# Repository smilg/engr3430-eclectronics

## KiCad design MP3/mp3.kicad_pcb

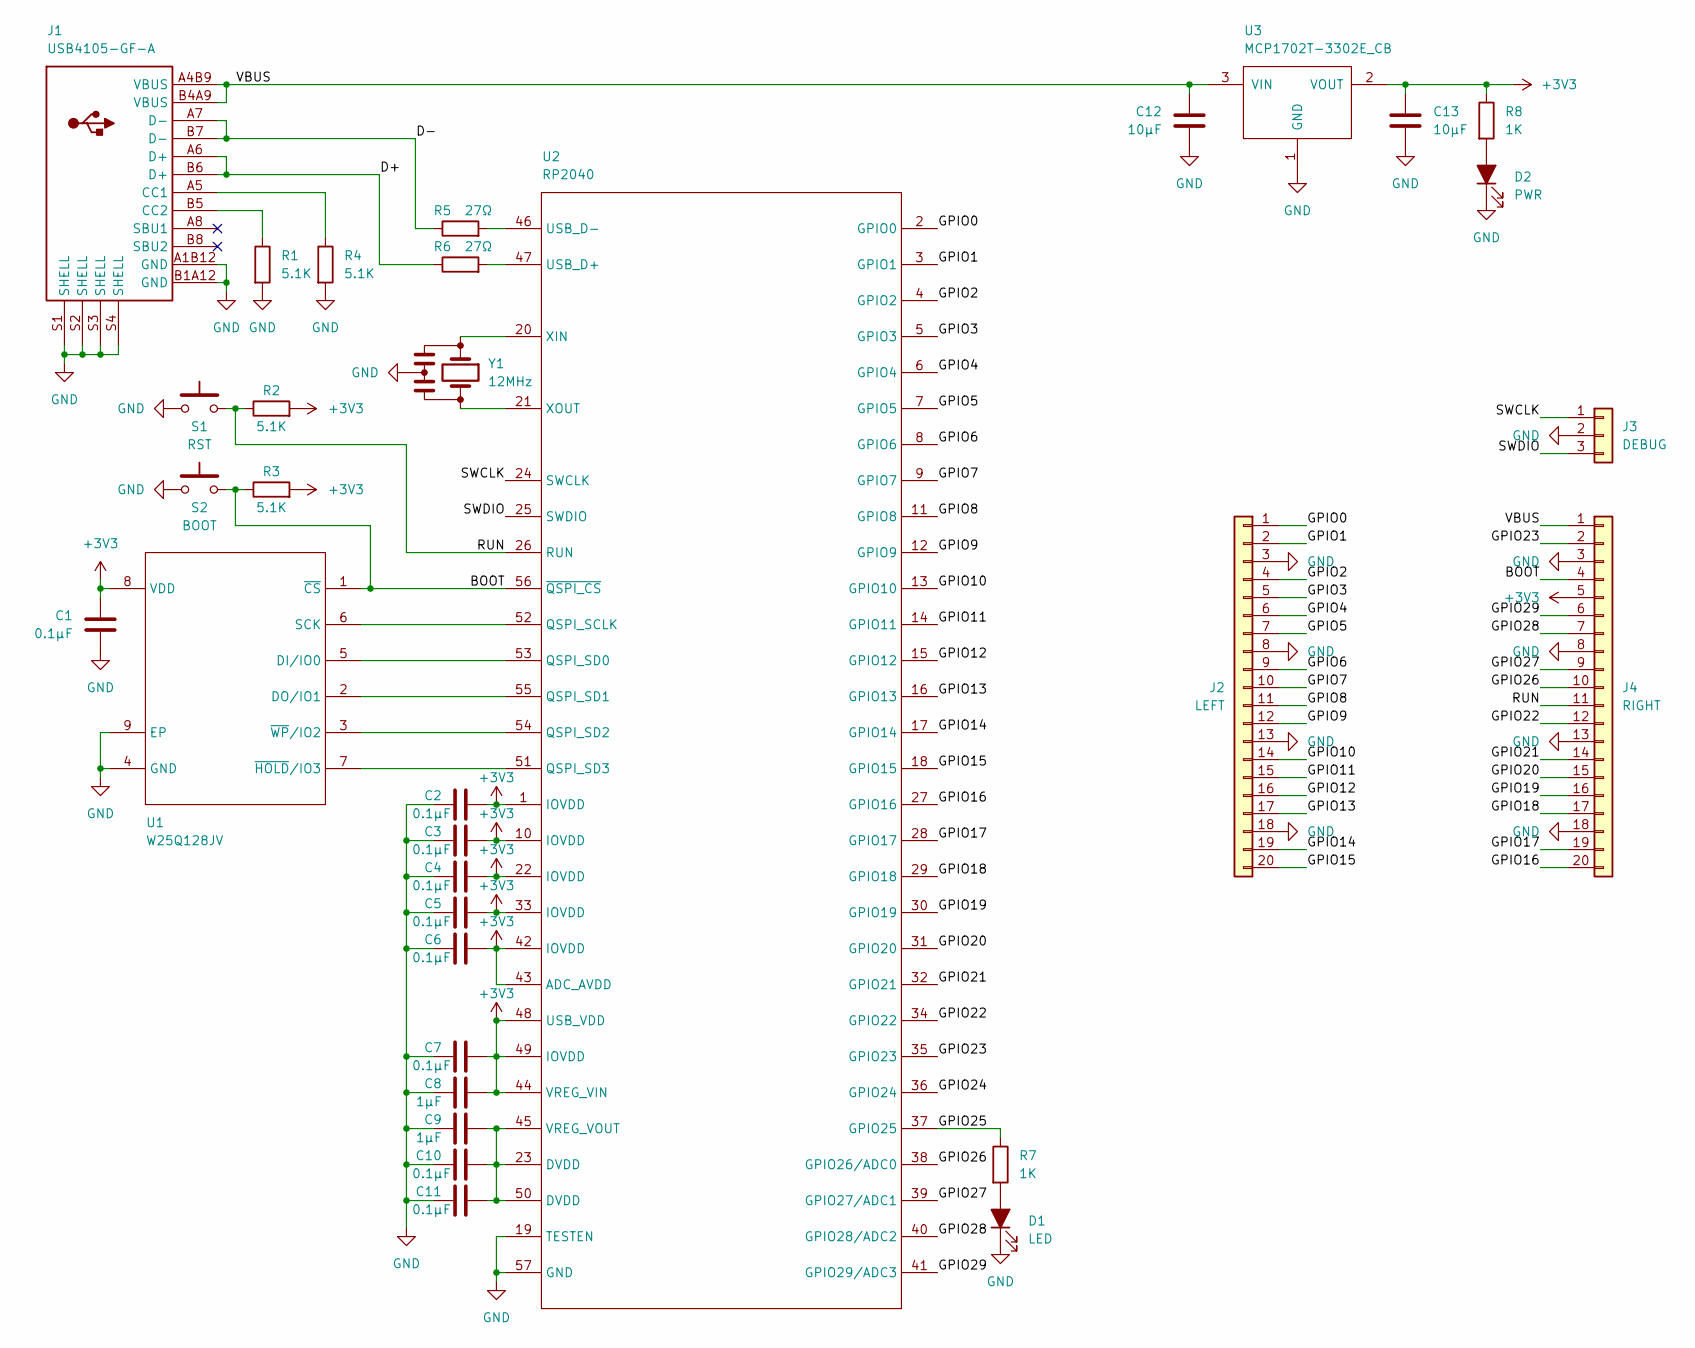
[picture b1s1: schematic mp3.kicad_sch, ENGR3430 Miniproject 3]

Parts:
C1, C2, C3, C4, C5, C6, C7, C10, C11: 0.1µF; C_0402_1005Metric
C8, C9: 1µF; C_0402_1005Metric
C12, C13: 10µF; C_0603_1608Metric
D1: LED; D_0805_2012Metric
D2: PWR; D_0805_2012Metric
J1: USB4105-GF-A
J2: LEFT; PinHeader_1x20_P2.54mm_Vertical
J3: DEBUG; PinHeader_1x03_P2.54mm_Vertical
J4: RIGHT; PinHeader_1x20_P2.54mm_Vertical
R1, R2, R3, R4: 5.1K; R_0402_1005Metric
R5, R6: 27Ω; R_0402_1005Metric
R7, R8: 1K; R_0402_1005Metric
S1: RST; KXT321LHS
S2: BOOT; KXT321LHS
U1: W25Q128JV; MIC_WSON-8
U2: RP2040
U3: MCP1702T-3302E_CB; SOT-23
Y1: 12MHz; CSTNE

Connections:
+3V3: C1.2, C2.1, C3.1, C4.1, C5.1, C6.1, C7.1, C8.1, C13.1, J4.5, R2.2, R3.2, R8.1, U1.8 (VDD), U2.1 (IOVDD), U2.10 (IOVDD), U2.22 (IOVDD), U2.33 (IOVDD), U2.42 (IOVDD), U2.43 (ADC_AVDD), U2.44 (VREG_VIN), U2.48 (USB_VDD), U2.49 (IOVDD), U3.2 (VOUT)
/BOOT: J4.4, R3.1, S2.2, U1.1 (~CS), U2.56 (~QSPI_CS)
/D+: J1.A6 (D+), J1.B6 (D+), R6.1
/D-: J1.A7 (D-), J1.B7 (D-), R5.1
/GPIO0: J2.1, U2.2 (GPIO0)
/GPIO1: J2.2, U2.3 (GPIO1)
/GPIO2: J2.4, U2.4 (GPIO2)
/GPIO3: J2.5, U2.5 (GPIO3)
/GPIO4: J2.6, U2.6 (GPIO4)
/GPIO5: J2.7, U2.7 (GPIO5)
/GPIO6: J2.9, U2.8 (GPIO6)
/GPIO7: J2.10, U2.9 (GPIO7)
/GPIO8: J2.11, U2.11 (GPIO8)
/GPIO9: J2.12, U2.12 (GPIO9)
/GPIO10: J2.14, U2.13 (GPIO10)
/GPIO11: J2.15, U2.14 (GPIO11)
/GPIO12: J2.16, U2.15 (GPIO12)
/GPIO13: J2.17, U2.16 (GPIO13)
/GPIO14: J2.19, U2.17 (GPIO14)
/GPIO15: J2.20, U2.18 (GPIO15)
/GPIO16: J4.20, U2.27 (GPIO16)
/GPIO17: J4.19, U2.28 (GPIO17)
/GPIO18: J4.17, U2.29 (GPIO18)
/GPIO19: J4.16, U2.30 (GPIO19)
/GPIO20: J4.15, U2.31 (GPIO20)
/GPIO21: J4.14, U2.32 (GPIO21)
/GPIO22: J4.12, U2.34 (GPIO22)
/GPIO23: J4.2, U2.35 (GPIO23)
/GPIO24: U2.36 (GPIO24)
/GPIO25: R7.1, U2.37 (GPIO25)
/GPIO26: J4.10, U2.38 (GPIO26/ADC0)
/GPIO27: J4.9, U2.39 (GPIO27/ADC1)
/GPIO28: J4.7, U2.40 (GPIO28/ADC2)
/GPIO29: J4.6, U2.41 (GPIO29/ADC3)
/RUN: J4.11, R2.1, S1.2, U2.26 (RUN)
/SWCLK: J3.1, U2.24 (SWCLK)
/SWDIO: J3.3, U2.25 (SWDIO)
/VBUS: C12.2, J1.A4B9 (VBUS), J1.B4A9 (VBUS), J4.1, U3.3 (VIN)
GND: C1.1, C2.2, C3.2, C4.2, C5.2, C6.2, C7.2, C8.2, C9.2, C10.2, C11.2, C12.1, C13.2, D1.1 (K), D2.1 (K), J1.A1B12 (GND), J1.B1A12 (GND), J1.S1 (SHELL), J1.S2 (SHELL), J1.S3 (SHELL), J1.S4 (SHELL), J2.3, J2.8, J2.13, J2.18, J3.2, J4.3, J4.8, J4.13, J4.18, R1.2, R4.2, S1.1, S2.1, U1.4 (GND), U1.9 (EP), U2.19 (TESTEN), U2.57 (GND), U3.1 (GND), Y1.2
unnamed: C9.1, C10.1, C11.1, U2.23 (DVDD), U2.45 (VREG_VOUT), U2.50 (DVDD)
unnamed: D1.2 (A), R7.2
unnamed: D2.2 (A), R8.2
unnamed: J1.A5 (CC1), R4.1
unnamed: J1.B5 (CC2), R1.1
unnamed: R5.2, U2.46 (USB_D-)
unnamed: R6.2, U2.47 (USB_D+)
unnamed: U1.2 (DO/IO1), U2.55 (QSPI_SD1)
unnamed: U1.3 (~WP/IO2), U2.54 (QSPI_SD2)
unnamed: U1.5 (DI/IO0), U2.53 (QSPI_SD0)
unnamed: U1.6 (SCK), U2.52 (QSPI_SCLK)
unnamed: U1.7 (~HOLD/IO3), U2.51 (QSPI_SD3)
unnamed: U2.20 (XIN), Y1.1
unnamed: U2.21 (XOUT), Y1.3

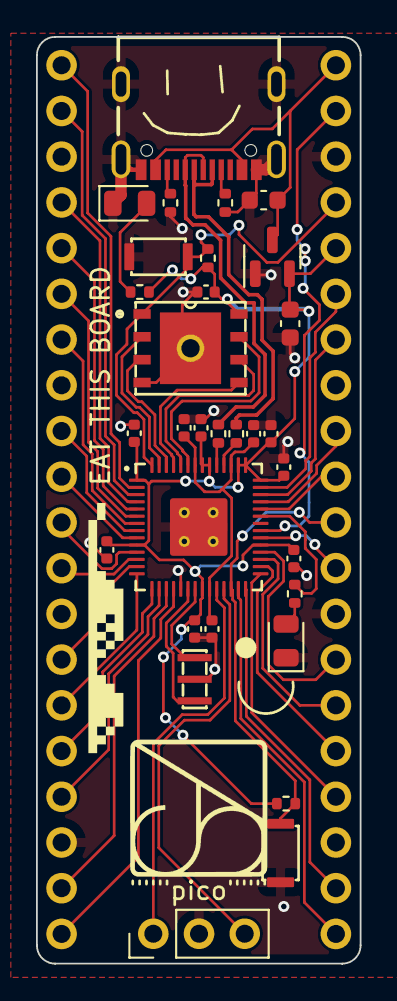
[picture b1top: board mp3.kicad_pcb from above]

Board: 2 copper layers, 18.0 x 51.5 mm, 34 parts (1 on the bottom side), 52 nets.

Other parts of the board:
OlinLogoLg: G***; OlinLogoLg

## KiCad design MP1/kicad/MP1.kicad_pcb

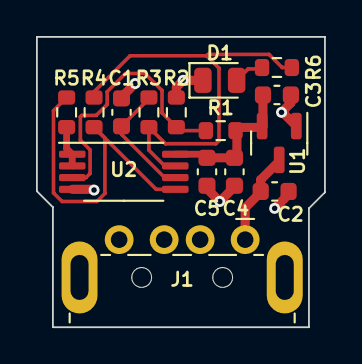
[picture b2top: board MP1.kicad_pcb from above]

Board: 2 copper layers, 16.0 x 16.1 mm, 15 parts (0 on the bottom side), 9 nets.

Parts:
C1, C5: 0.1μF; C_0603_1608Metric
C2, C3, C4: 1μF; C_0603_1608Metric
D1: LED; D_0805_2012Metric
J1: USB_A; USB_A_Molex_48037
R1: 10KΩ; R_0603_1608Metric
R2: 14.3KΩ; R_0603_1608Metric
R3: 3.01MΩ; R_0603_1608Metric
R4: 9530Ω; R_0603_1608Metric
R5: 20KΩ; R_0603_1608Metric
R6: 69.8Ω; R_0603_1608Metric
U1: MCP1702-3302E_SOT23; SOT-23
U2: MCP6022; TSSOP-8_4.4x3mm_P0.65mm

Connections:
+5V: C2.1, J1.1 (VBUS), U1.3 (VI)
/Vcc: C3.1, C4.1, C5.1, R1.1, U1.2 (VO), U2.8 (V+)
/Vref: R5.2, U2.1, U2.2 (-)
GND: C1.2, C2.2, C3.2, C4.2, C5.2, D1.1 (K), J1.4 (GND), J1.5 (Shield), R2.2, U1.1 (GND), U2.4 (V-)
unnamed: C1.1, R3.1, U2.6 (-)
unnamed: D1.2 (A), R6.2
unnamed: R1.2, R2.1, U2.3 (+)
unnamed: R3.2, R4.1, R6.1, U2.7
unnamed: R4.2, R5.1, U2.5 (+)

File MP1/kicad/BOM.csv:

Reference, Value, Footprint, Datasheet, Digikey Part #
"C1","0.1μF","Capacitor_SMD:C_0603_1608Metric","","311-1779-1-ND"
"C2","1μF","Capacitor_SMD:C_0603_1608Metric","","399-7376-1-ND"
"C3","1μF","Capacitor_SMD:C_0603_1608Metric","","399-7376-1-ND"
"C4","1μF","Capacitor_SMD:C_0603_1608Metric","","399-7376-1-ND"
"C5","0.1μF","Capacitor_SMD:C_0603_1608Metric","","311-1779-1-ND"
"D1","LED","Diode_SMD:D_0805_2012Metric","https://optoelectronics.liteon.com/upload/download/DS22-2000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","160-1427-1-ND"
"J1","USB_A","MP1:USB_A_Molex_48037","https://www.molex.com/pdm_docs/sd/480370001_sd.pdf","WM17117-ND"
"R1","10KΩ","Resistor_SMD:R_0603_1608Metric","","311-10.0KHRCT-ND"
"R2","14.3KΩ","Resistor_SMD:R_0603_1608Metric","","311-14.3KHRCT-ND"
"R3","3.01MΩ","Resistor_SMD:R_0603_1608Metric","","311-3.01MHRCT-ND"
"R4","9530Ω","Resistor_SMD:R_0603_1608Metric","","311-9.53KHRCT-ND"
"R5","20KΩ","Resistor_SMD:R_0603_1608Metric","","311-20.0KHRCT-ND"
"R6","69.8Ω","Resistor_SMD:R_0603_1608Metric","","311-69.8HRCT-ND"
"U1","MCP1702-3302E_SOT23","Package_TO_SOT_SMD:SOT-23","https://ww1.microchip.com/downloads/en/DeviceDoc/22008E.pdf","MCP1702T-3302E/CBCT-ND"
"U2","MCP6022","Package_SO:TSSOP-8_4.4x3mm_P0.65mm","http://ww1.microchip.com/downloads/en/devicedoc/20001685e.pdf","MCP6022T-I/STCT-ND"

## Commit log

2022-09-16 add mp1
2022-09-16 add mp1 bom
2022-10-04 add mp3 files
2022-10-06 round corners, move termination resistors close to rp2040
2022-10-06 fix via too close to memory 3.3v pad
2022-10-06 refill ground planes
2022-10-07 move C10 down a little for looks
2022-10-31 add interactive bom
